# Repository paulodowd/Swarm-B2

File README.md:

<p align="center">
<br>
</img>
</img>
<br>
</p>

# Swarm-B2
Infra-red (IR) Communication board for Pololu 3Pi+ robots that also has a pin header to interface with an M5 Stack Core2.  This is the second major design of such a board, hence the name (S)warm (B)oard 2 - SwarmB2.  A third version is under-development with the intention to supercede this design ([SwarmB3](https://github.com/paulodowd/SwarmB3)). 

The board functions as an i2c device, so it should be relatively easy to integrate into other projects using 5v, ground, SCK and SDA connections.  The board can communicate with other SwarmB2 boards up to about 2.5m max, or down to less than a centimetre.  The firmware for the board has been written with the intention that all (or most) configuration parameters can be set at runtime, so reprogramming firmware shouldn't be necessary.

## Features
- 32 bytes per message.
- SLIP-style encoding/escaping.
- 9600 or 4800 baudrate (device dependent)
- Receive or transmit, cannot do both concurrently.
- Receiving is polled across 4 receivers.
- Transmission power set by a potentiometer (0-2.5m)
- Message framing with start delimiter and message length embedded.
- A 16 bit CRC to detect transmission errors.
- Error statistics at message level.
- Performance statitics (timings, etc).
- Bearing estimation.
- 3x LDR and 2x Sharp IR Range Finder integration on PCB.
- Reconfigurable communication strategies/priorities.
- Header pins to attach to a Pololu 3Pi+ robot.
- Header pins for an M5Stack Core2 device interfacing.

## Getting Started

The best way to get started is to download and install the example <a href="https://github.com/paulodowd/Swarm-B2/tree/main/examples/M5Visualiser">M5Visualiser</a> written for the M5Stack Core2.  This example demonstrates how to make function calls through the `SwarmB2_c` class. The class has function calls for all functionality available on the Swarm-B2, returning data types specified in the file `ircomm_i2c.h`.  

## Working with the M5Stack Core2

To get started with the M5Stack Core2, it is best to follow the manufacturers documentation to configure the Arduino IDE.  Make sure you follow the instructions for both:
- <a href="https://docs.m5stack.com/en/arduino/arduino_board">Board Management Installation</a>
- <a href="https://docs.m5stack.com/en/arduino/arduino_library">Arduino Library Installation</a>

The <a href="https://github.com/paulodowd/Swarm-B2/tree/main/examples/M5Visualiser">M5Visualiser</a> example was written against the M5Unified library - installing or using a different M5Stack library is likely to cause compilation errors for the provided example.

## Important Characteristics

### Message Size
The Swarm-B2 can receive a message of maximum length 32 bytes to transmit.  This limitation is currently defined by the Arduino i2c implementation.  The Swarm-B2 can accept a message of upto 32bytes, and it will then encode the message using a further number of bytes.   It is important to consider that when transmitting a long length message, the probability that the message will become corrupted (or similar) increases.  

### Polling

The Swarm-B2 board can only read one receiver at a time. The board is configured by default to switch which receiver is enabled as soon as one message is successfully received.  The board is also configured by default to switch receiver if it detects no activity.  Otherwise, the board is configured by default to listen for a period of time before switching receiver. 

### Transmitting
The Swarm-B2 must disable receiving to be able to transmit, otherwise it will immediately receive it's own transmission.  Therefore, the board is configured to periodically transmit messages, and in the interval period poll the receivers to receive messages.  

### Transmitting Power
The power of the IR LEDs which transmit messages can be varied via the blue potentiometer on the back of the Swarm-B2 circuit board.  The blue potentiometer has a small silver dot: rotating the white arrow indicator to point at this silver dot will produce maximum power, or maximum range of transmission.  Swarm-B2 can transmit upto 3m distance.  However, this is not very useful in a swarm/multi-robot context.  If the transmit power is set high, it is likely that the environment will become saturated with IR emissions, effectively blocking transmissions between all other robots.  The recommended position for the potentiometer is indicated in the below image with a pink dot.  This position sets the communication distance to approximately 20cm, or two robot-body lengths.

### Other Configurations
It is possible to change the Swarm-B2 configuration via i2c transactions.  For example, it is possible to setup a Swarm-B2 to only transmit continously.  Or, it is possible to setup the Swarm-B2 to only receive on 1 receiver continuously.  

## FAQ

## Using the Swarm-B2 board in other Projects
This IR communication board can be used as a general purpose communication board.  The firmware on this github page is written as an i2c slave device with address `0x11`.  It should be possible to use the IR Communication board in it's current design and format with any other device that can operate the I2C protocol.  To do so, you simply need to connect the `5v`, `GND`, `SCL` and `SDA` pins appropriately to your operating device.  These physical pins are labelled on the underside of the circuit board as `+RED` (5v), `-BLK` (GND), `SDA` and `SCL`, or as `5V`, `GND`, `SCL`, `SDA` on the  topside of the circuit board.

## Fabrication, Gerber files
Navigate to folder `pcb` to find the last known gerber files sent for manufacturing, `Gerbers.zip`.  

## Schematic
The schematic of the communication board is available in picture format in the `images` folder and within the pcb folder as KiCad files.

## Interesting Information

IR communication is implemented using the standard Serial (hardware UART) functionality common to Arduino (e.g. `Serial.print()`), and so the IR circuit is electronically connected to  the Arduino TX and RX pins.  The detection (receiving) circuit uses a Demodulator chip that is tuned for a carrier frequency of 38.4Khz or 57.6Khz (more details below).  Therefore, the Arduino Nano generates a 38Khz or 58Khz signal via an internal timer interrupt to provide the transmitting carrier, output on digital pin 4.  

The carrier signal is combined electronically with the TX pin state through an OR gate (74xx32). The logic (OR) of this operation is defined by the gates sinking the current through the tranmitting IR LEDs.  Therefore, the LEDs are not driven by the 74xx32 (or the Arduino Nano, to be clear), and are considered active low.  A nice unintended side effect of this is that when TX is inactive (LOW, not transmitting), the 74xx32 output is HIGH despite the continued 38Khz signal generation - which means the IR LEDs are off and not saturating the environment.

In this circuit design, a single gate is used to sink current.  It might be important to note that the <a href="https://www.ti.com/lit/ds/symlink/sn54hc32-sp.pdf">datasheet</a> for the logic gates specifies a max current sink of 50ma through ground - and here we are potentially sinking upto 200ma from the 4 IR LEDs.    So far, I've not seen any significant changes to performance and this may be because I am not sinking current continuously, instead intermitently at 38Khz. All 4 OR gates within the 74xx32 are ganged, but the internal ground connection may still be a limitation. In either case, I haven't yet seen any problems or difference in performance.  It might be unwise to active the IR LEDs continuously (i.e. not modulated).

### Important Considerations

- **IR Demodulator:** I tried a few IR demodulator chips and they are not all created equally.  In particular, those designed to receive bursts of transmission appear poorly suited.  When using ones for burst transmission, I observed that I had to wave the transmitter or receiver around to get a successful transmission (perhaps some inner circuitry reaches a saturation?).  Instead it is better to use those designed for continuous transmission. The Vishay **TSDP34138** (<a href="https://www.farnell.com/datasheets/2245004.pdf">datasheet</a>) seems to fit this and works well / reliably.  The datasheet specifies upto 4800 baud for a 38.4Khz carrier frequency.  If you want to reproduce this board, I recommend you use the same device, or be ready for some trials of different devices.
- **Self-Receiving:** I did have an issue of a single board receiving it's own IR transmissions, and not being able to receive transmission from neighbours.  I believe this is because the UART implementation (on the Atmega328 at least) operates send (TX) and receive (RX) independently.  When using IR light, this means it will detect it's own transmission. After attempting a lot of different solutions, it was as simple as disabling the RX functionality of the UART by a register operation.  I'm glad this was available!  You can review the details of this on page 171 of the Atmega328 datasheet (<a href="https://ww1.microchip.com/downloads/en/DeviceDoc/Atmel-7810-Automotive-Microcontrollers-ATmega328P_Datasheet.pdf">here</a>).  
- **Programming the Arduino Nano:** It is important to note that the programming of the Arduino Nano will most often fail if the IR Demodulator is electronically connected.  Therefore, the circuit design has a jumper (labelled, "RX Break") intended for a connecting removable sleeve, to allow the connection to be broken for programming.  Importantly, no IR messages can be received if this jumper is not closed with the sleeve.  
- **Buffer Sizes:** The main limitation on the size of a string that can be sent over IR is actually the number of bytes that can be transferred on the I2C bus.  I think this is dependent on the Arduino Wire library and could be modifed. Or, strings to transmit could be broken into parts to transfer over I2C.  A second consideration is that the Arduino UART device has a buffer of 64 bytes.  For simplicity, the software current has buffers of 32 bytes.

## Notes on Using a M5Stack Core2

- The docs for the M5Stack Core2 are at this <a href="https://docs.m5stack.com/en/core/core2">link</a>.
- Follow the guides at <a href="https://docs.m5stack.com/en/arduino/arduino_ide">this link</a> to setup the Arduino IDE.

## Links and resources I have found useful
- Example code and discussion for different CRC algorithms: <a href="https://www.sunshine2k.de/articles/coding/crc/understanding_crc.html">link</a>
- Interesting Arduino forum post debugging CRC: <a href="https://forum.arduino.cc/t/crc-8-i2c-cyclic-redundancy-check/644812/4">link</a>
- Microchip Application Note with CRC: <a href="https://ww1.microchip.com/downloads/en/AppNotes/00730a.pdf">link</a>
- Discussion on CRC and data length: <a href="https://stackoverflow.com/questions/2321676/data-length-vs-crc-length">link</a>
- Some information on UART Baudrates: <a href="https://lucidar.me/en/serialib/most-used-baud-rates-table/">link</a>
- Discussion on start/stop bit and errors with UART: <a href="https://electronics.stackexchange.com/questions/91450/what-exactly-is-the-start-bit-error-in-uart">link</a>
- Disucssion on catching frame data overrun in UART: <a href="https://forum.arduino.cc/t/rs232-uart-frame-data-overrun-error-handling/193266/12">link</a>
- Table of ASCII values: <a href="https://www.ascii-code.com/">link</a>

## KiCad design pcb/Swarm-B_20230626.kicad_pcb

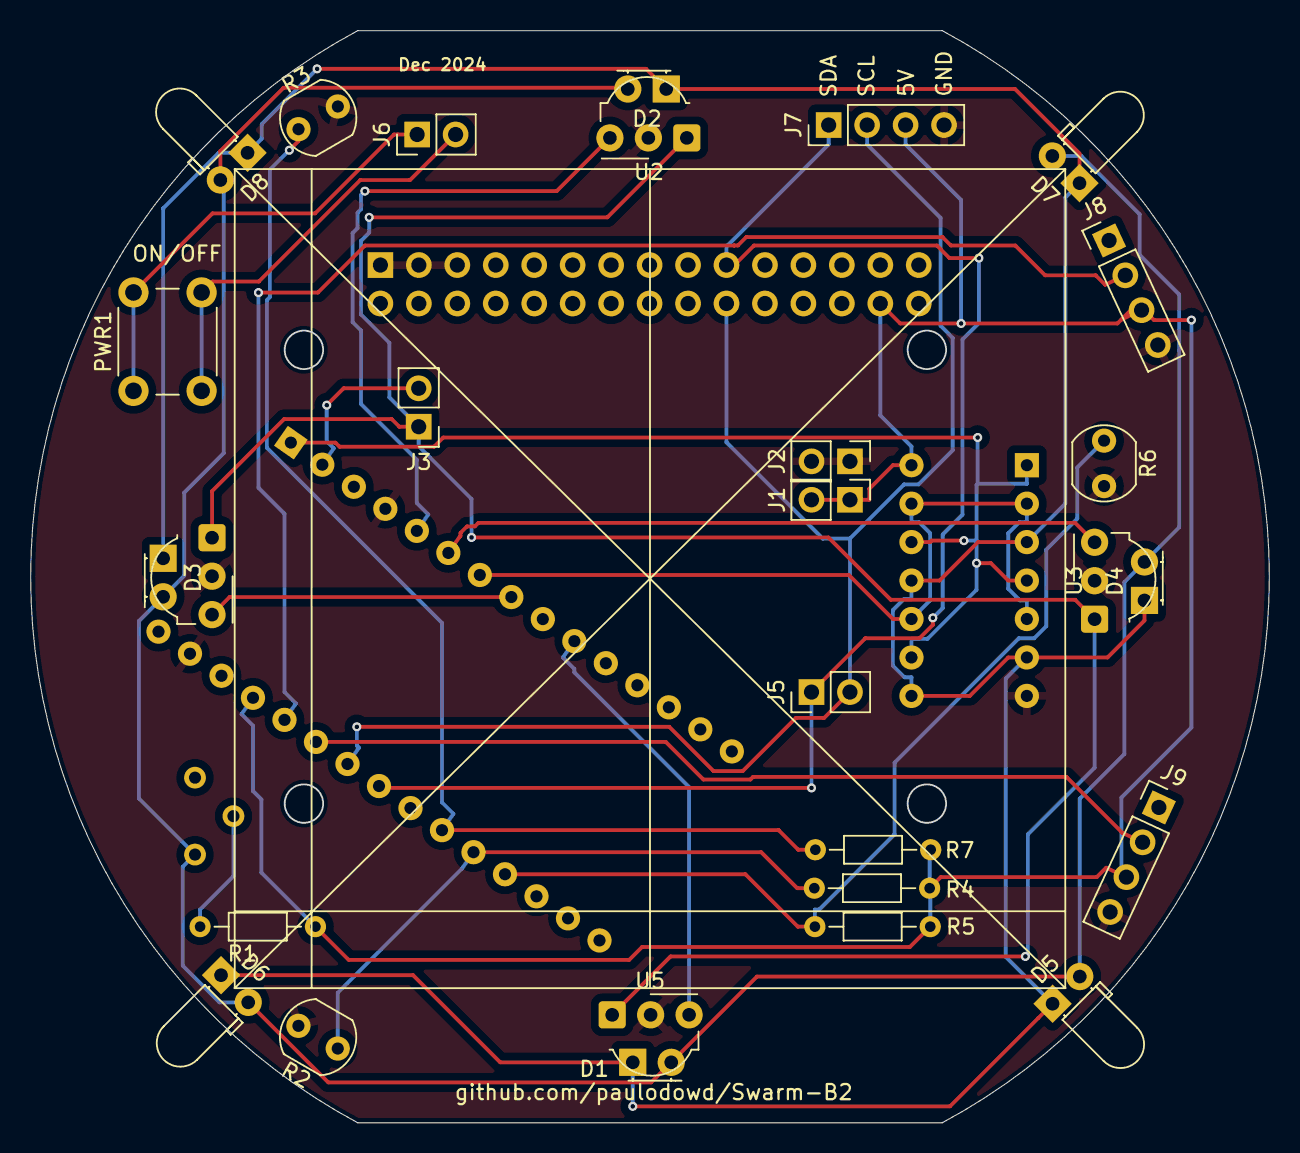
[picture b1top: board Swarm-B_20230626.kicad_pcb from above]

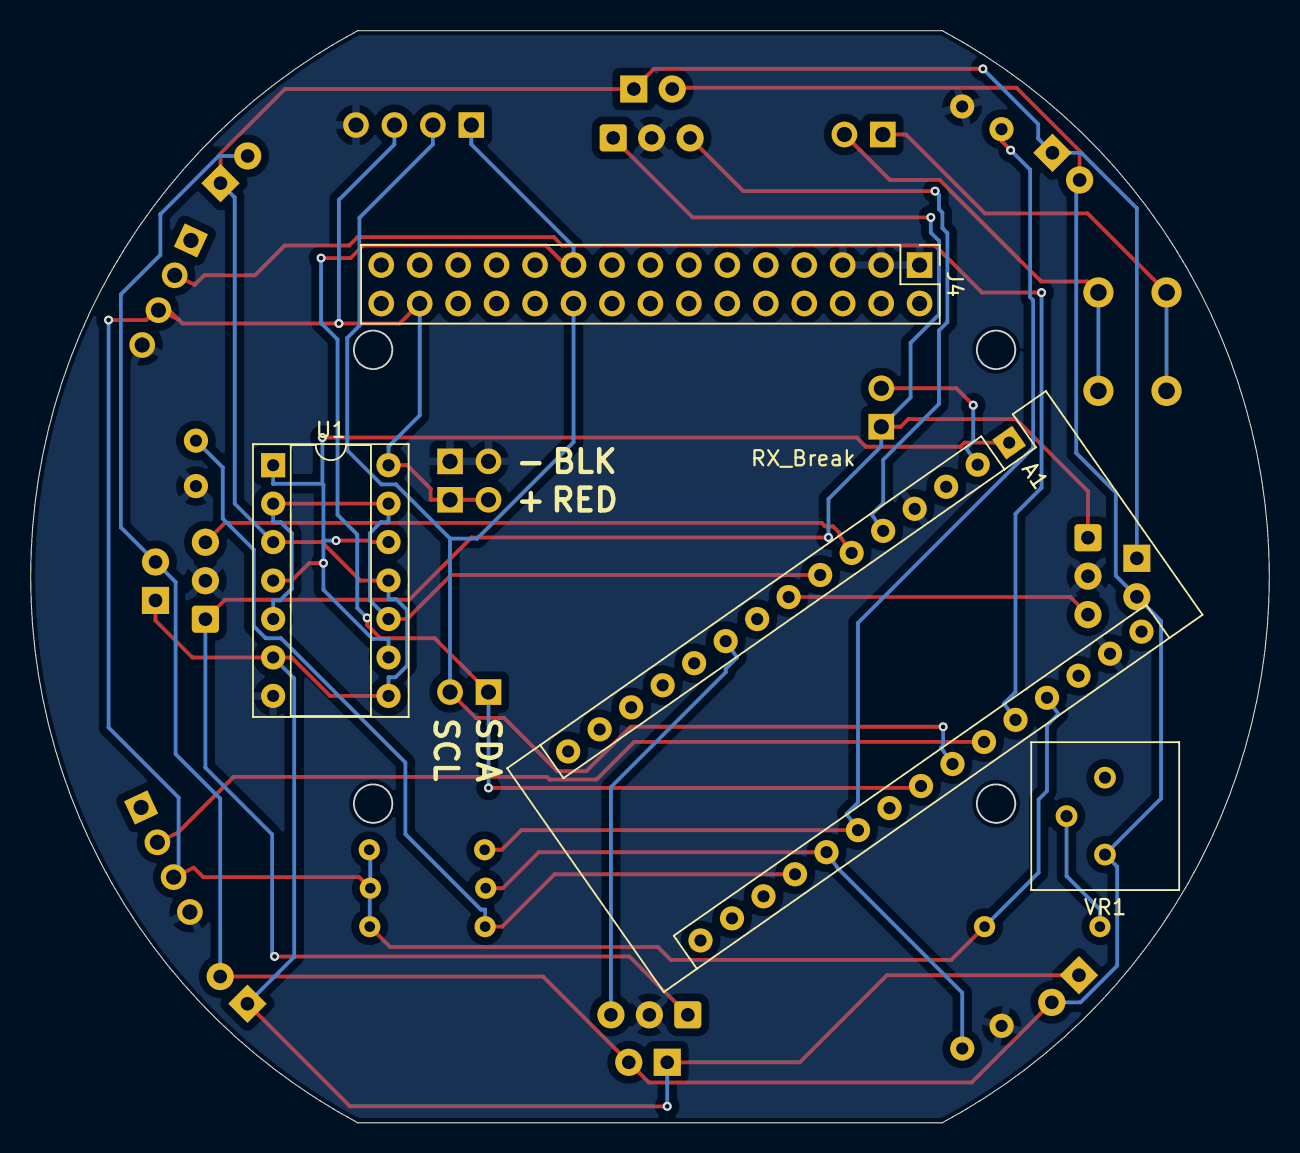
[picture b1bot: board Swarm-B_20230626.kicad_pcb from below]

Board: 2 copper layers, 81.7 x 72.1 mm, 32 parts (4 on the bottom side), 22 nets.

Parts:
A1: Arduino_Nano_v3.x; Arduino_Nano
D1, D2, D3, D4, D5, D6, D7, D8: IR_LED; LED_D3.0mm_Horizontal_O1.27mm_Z2.0mm
J1: 5v_3Pi; PinHeader_1x02_P2.54mm_Vertical
J2: GND_3Pi; PinHeader_1x02_P2.54mm_Vertical
J3: RX_Break; PinHeader_1x02_P2.54mm_Vertical
J4: Conn_02x15_Top_Bottom; PinHeader_2x15_P2.54mm_Vertical
J5: I2C_3Pi; PinHeader_1x02_P2.54mm_Vertical
J6: 3PI_SWTCH; PinHeader_1x02_P2.54mm_Vertical
J7: I2C_Exp; PinHeader_1x04_P2.54mm_Vertical
J8: ProxA; PinHeader_1x04_P2.54mm_Vertical
J9: ProxB; PinHeader_1x04_P2.54mm_Vertical
PWR1: Bttn; SW_PUSH_6mm
R1: 15R_IRLED; R_Axial_DIN0204_L3.6mm_D1.6mm_P7.62mm_Horizontal
R2, R3, R6: LDR; R_LDR_5.0x4.1mm_P3mm_Vertical
R4, R5, R7: 10K_LDR; R_Axial_DIN0204_L3.6mm_D1.6mm_P7.62mm_Horizontal
U1: 74LS32; DIP-14_W7.62mm_Socket
U2, U3, U4, U5: TSDP34138; Vishay_MOLD-3Pin
VR1: 1K_Pot_IRLED; Potentiometer_Bourns_3386P_Vertical

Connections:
+5V: A1.27 (+5V), J1.1, J1.2, J4.28, J7.3, J8.3, J9.3, R1.1, R4.1, R5.1, R7.1, U1.14 (VCC)
GND: A1.4 (GND), A1.29 (GND), J2.1, J2.2, J4.1, J4.3, J4.5, J7.4, J8.4, J9.4, R2.2, R3.2, R6.2, U1.7 (GND), U2.2 (GND), U3.2 (GND), U4.2 (GND), U5.2 (GND)
unnamed: A1.19 (A0), R5.2, R6.1
unnamed: A1.20 (A1), R2.1, R4.2
unnamed: A1.21 (A2), R3.1, R7.2
unnamed: A1.23 (A4), J4.19, J5.1, J7.1
unnamed: A1.24 (A5), J4.20, J5.2, J7.2
unnamed: A1.25 (A6), J9.2
unnamed: A1.26 (A7), J8.2
unnamed: A1.2 (D0/RX), J3.2
unnamed: A1.1 (D1/TX), U1.1, U1.4, U1.9, U1.12
unnamed: A1.5 (D2), U2.3 (Vs)
unnamed: A1.6 (D3), U3.3 (Vs)
unnamed: A1.7 (D4), U1.2, U1.5, U1.10, U1.13
unnamed: A1.8 (D5), U4.3 (Vs)
unnamed: A1.10 (D7), U5.3 (Vs)
unnamed: D1.2 (A), D2.2 (A), D3.2 (A), D4.2 (A), D5.2 (A), D6.2 (A), D7.2 (A), D8.2 (A), VR1.3 (CW)
unnamed: D1.1 (K), D2.1 (K), D3.1 (K), D4.1 (K), D5.1 (K), D6.1 (K), D7.1 (K), D8.1 (K), U1.3, U1.6, U1.8, U1.11
unnamed: J6.1, PWR1.1
unnamed: J6.2, PWR1.2
unnamed: J3.1, U2.1 (OUT), U3.1 (OUT), U4.1 (OUT), U5.1 (OUT)
unnamed: R1.2, VR1.2 (WIPER)

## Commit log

2024-06-20 significant changes to nano firmware
2025-12-03 Implemented an escape routine for the start byte, need to put back the tracking of rx errors for metrics
2025-12-23 Big restructuring. Implementing Arduino master side class
2025-12-27 moved nano-neo from timer2 to timer1. Need to do the same with nano
2026-03-01 Revise README for SwarmB2 with features and usage
    Updated README with detailed features, usage instructions, and important considerations for the SwarmB2 IR Communication board.
2026-03-01 Document future improvements for the board design
    Added section on improvements for future revisions of the board, including suggestions for additional features and hardware changes.
2026-03-02 In nano-neo, removed boolean flags to instead check for 0 values for associated variables. Added small helper functions to improve code readability.
2026-03-02 Clean up README formatting and image tags
    Added a bit of text about modifying NeoHWSerial.
2026-03-02 Project has a dependency on my own modification to NeoHWSerial, so I've included the modified library keeping the original license information and attribution.
2026-03-02 removing old nano firmware, it is very out of date
2026-03-03 Add SwarmB2 configuration section to README
    Added section on SwarmB2 configuration details and clarified concurrent operation limitations.
2026-03-03 Enhance SwarmB2 configuration details in README
    Expanded the SwarmB2 configuration section to include details on transmission priorities and message repetition.
2026-03-27 Potential bug fix in ircomm.cpp, line 670
2026-04-17 I think disableRx had a bug where the serial object buffer was not flushed. I've stripped out more parameters in an attmept to simplify things.
2026-04-19 add a new 1 byte message status feature so that the board can be polled quickly.
2026-04-21 Implemented and tested a polling for messages feature.
2026-04-21 removed NeoHWSerial from the project. I'll investigate frame errors on the SwarmB3 board instead
2026-04-24 Found a bug in the parser class where it wasn't reporting one byte received if the byte received was just an intermediate byte in the paylod. That would have been effecting the activity log, and the 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
2026-05-07 updated parser class to return a struct, which simplifies the update() in ircomm. Updated bearing to resolve against the theoretic max bytes that can be received, so the vectors will contain a value 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
2026-05-18 Enhance README with configuration and usage info
    Updated README to include additional configuration details and usage instructions for the Swarm-B2 board.
2026-05-18 Fix formatting of predict_multi description in README
2026-05-18 updated setTxPeriod() to take into account the transmission repeats by implementing getTxTotalLength()
